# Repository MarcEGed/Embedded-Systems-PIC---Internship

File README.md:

Space invaders embedded systems project
Includes drivers, api, scheduler and main file

Written for PIC18F46K22

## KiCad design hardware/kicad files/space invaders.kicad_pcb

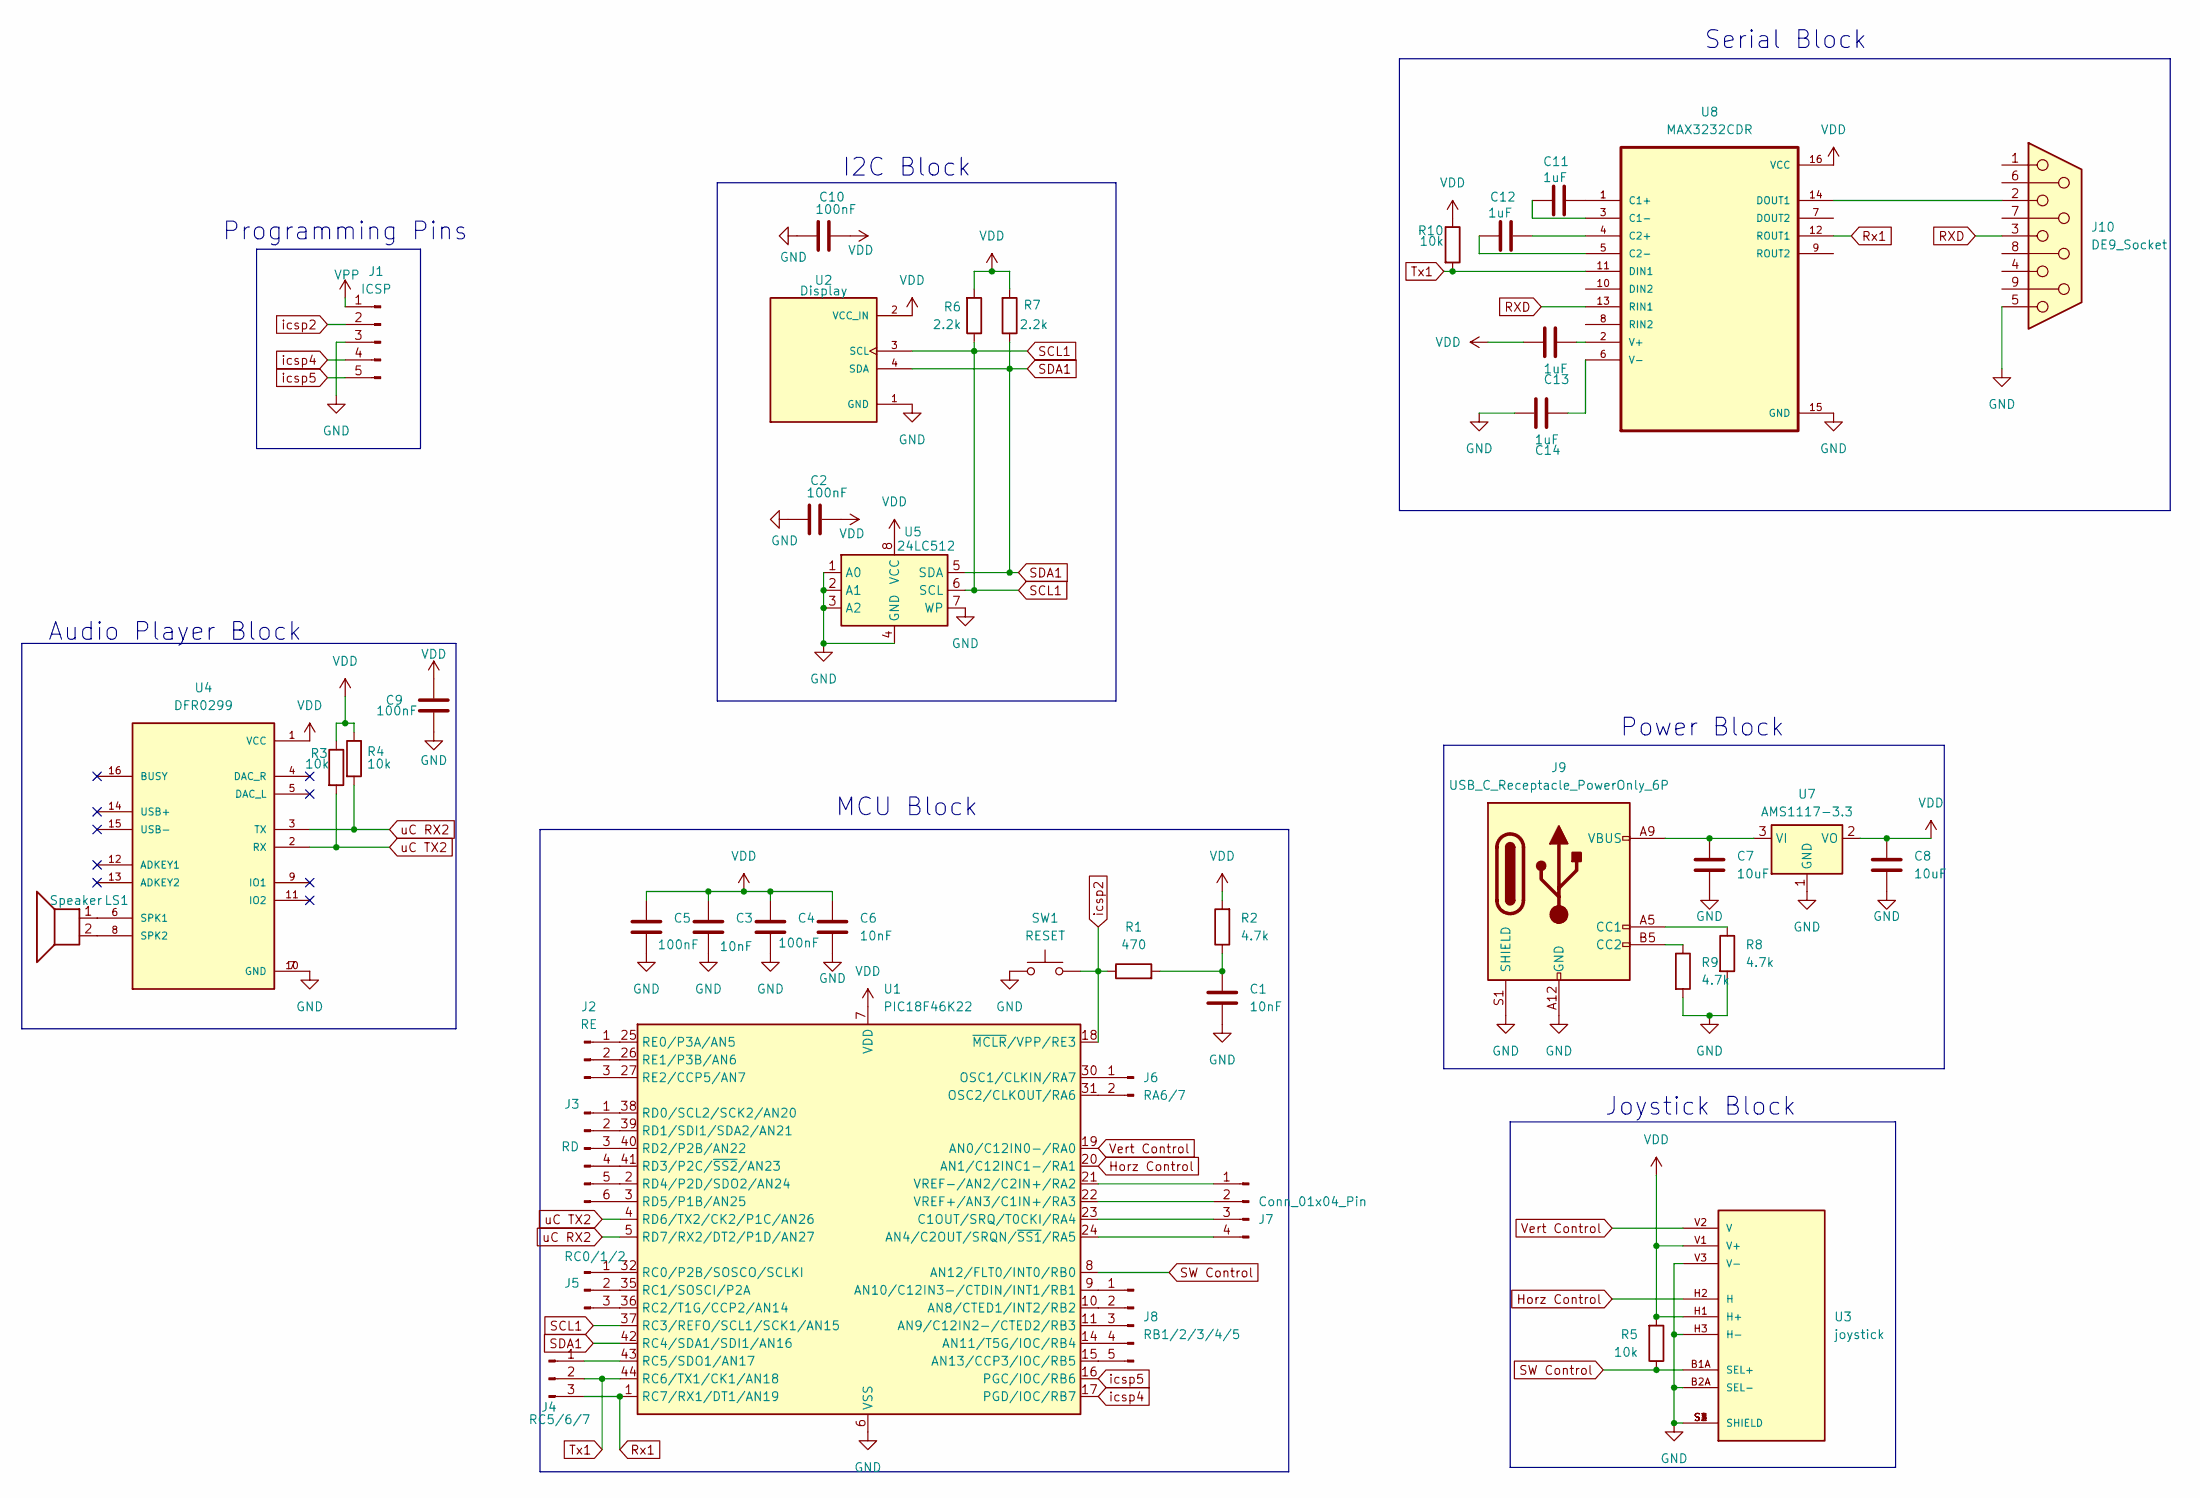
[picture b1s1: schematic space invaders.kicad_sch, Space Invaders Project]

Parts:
C1, C3, C6: 10nF; C_0603_1608Metric
C2, C4, C5, C9, C10: 100nF; C_0603_1608Metric
C7, C8: 10uF; C_0603_1608Metric
C11, C12, C13, C14: 1uF; C_0603_1608Metric
J1: ICSP; PinHeader_1x05_P2.54mm_Vertical
J2: RE; PinHeader_1x03_P2.54mm_Vertical
J3: RD; PinHeader_1x06_P2.54mm_Vertical
J4: RC5/6/7; PinHeader_1x03_P2.54mm_Vertical
J5: RC0/1/2; PinHeader_1x03_P2.54mm_Vertical
J6: RA6/7; PinHeader_1x02_P2.54mm_Vertical
J7: Conn_01x04_Pin; PinHeader_1x04_P2.54mm_Vertical
J8: RB1/2/3/4/5; PinHeader_1x05_P2.54mm_Vertical
J9: USB_C_Receptacle_PowerOnly_6P; USB_C_Receptacle_Amphenol_12401610E4-2A
J10: DE9_Socket; DSUB-9_Pins_Horizontal_P2.77x2.84mm_EdgePinOffset7.70mm_Hou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
LS1: Speaker; Speaker_CUI_CMR-1206S-67
R1: 470; R_0603_1608Metric
R2, R8, R9: 4.7k; R_0603_1608Metric
R3, R4, R5, R10: 10k; R_0603_1608Metric
R6, R7: 2.2k; R_0603_1608Metric
SW1: RESET; SW_PUSH_6mm_H4.3mm
U1: PIC18F46K22; TQFP-44_10x10mm_P0.8mm
U2: Display; MODULE_DM-OLED096-636; PARTREV 2018-09-10
U3: joystick; XDCR_COM-09032; PARTREV N/A
U4: DFR0299; MODULE_DFR0299
U5: 24LC512; SOIC-8-1EP_3.9x4.9mm_P1.27mm_EP2.41x3.3mm
U7: AMS1117-3.3; SOT-223-3_TabPin2
U8: MAX3232CDR; SOIC-16_3.9x9.9mm_P1.27mm

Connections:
GND: C1.2, C2.2, C3.2, C4.2, C5.2, C6.2, C7.1, C8.2, C9.2, C10.2, C14.1, J1.3, J9.A12 (GND), J9.B12 (GND), J9.S1 (SHIELD), J10.5, R8.2, R9.2, SW1.1, U1.6 (VSS), U1.29 (VSS), U2.1 (GND), U3.B2A (SEL-), U3.H3 (H-), U3.S1 (SHIELD), U3.S2 (SHIELD), U3.S3 (SHIELD), U3.S4 (SHIELD), U3.V3 (V-), U4.7 (GND), U4.10 (GND), U5.1 (A0), U5.2 (A1), U5.3 (A2), U5.4 (GND), U5.7 (WP), U7.1 (GND), U8.15 (GND)
Horz Control: U1.20 (AN1/C12INC1-/RA1), U3.H2 (H)
unnamed: C1.1, R1.2, R2.1
unnamed: J2.1, U1.25 (RE0/P3A/AN5)
unnamed: J2.2, U1.26 (RE1/P3B/AN6)
unnamed: J2.3, U1.27 (RE2/CCP5/AN7)
unnamed: J3.1, U1.38 (RD0/SCL2/SCK2/AN20)
unnamed: J3.2, U1.39 (RD1/SDI1/SDA2/AN21)
unnamed: J3.3, U1.40 (RD2/P2B/AN22)
unnamed: J3.4, U1.41 (RD3/P2C/~SS2/AN23)
unnamed: J3.5, U1.2 (RD4/P2D/SDO2/AN24)
unnamed: J3.6, U1.3 (RD5/P1B/AN25)
unnamed: J4.1, U1.43 (RC5/SDO1/AN17)
unnamed: J5.1, U1.32 (RC0/P2B/SOSCO/SCLKI)
unnamed: J5.2, U1.35 (RC1/SOSCI/P2A)
unnamed: J5.3, U1.36 (RC2/T1G/CCP2/AN14)
unnamed: J6.1, U1.30 (OSC1/CLKIN/RA7)
unnamed: J6.2, U1.31 (OSC2/CLKOUT/RA6)
unnamed: J7.1, U1.21 (VREF-/AN2/C2IN+/RA2)
unnamed: J7.2, U1.22 (VREF+/AN3/C1IN+/RA3)
unnamed: J7.3, U1.23 (C1OUT/SRQ/T0CKI/RA4)
unnamed: J7.4, U1.24 (AN4/C2OUT/SRQN/~SS1/RA5)
unnamed: J8.1, U1.9 (AN10/C12IN3-/CTDIN/INT1/RB1)
unnamed: J8.2, U1.10 (AN8/CTED1/INT2/RB2)
unnamed: J8.3, U1.11 (AN9/C12IN2-/CTED2/RB3)
unnamed: J8.4, U1.14 (AN11/T5G/IOC/RB4)
unnamed: J8.5, U1.15 (AN13/CCP3/IOC/RB5)
unnamed: J9.A5 (CC1), R8.1
unnamed: J9.B5 (CC2), R9.1
unnamed: LS1.1, U4.6 (SPK1)
unnamed: LS1.2, U4.8 (SPK2)
unnamed: C7.2, J9.A9 (VBUS), J9.B9 (VBUS), U7.3 (VI)
unnamed: C11.1, U8.1 (C1+)
unnamed: C11.2, U8.3 (C1-)
unnamed: C12.1, U8.4 (C2+)
unnamed: C12.2, U8.5 (C2-)
unnamed: J10.2, U8.14 (DOUT1)
unnamed: C13.2, U8.2 (V+)
unnamed: C14.2, U8.6 (V-)
RXD: J10.3, U8.13 (RIN1)
Rx1: J4.3, U1.1 (RC7/RX1/DT1/AN19), U8.12 (ROUT1)
SCL1: R6.1, U1.37 (RC3/REFO/SCL1/SCK1/AN15), U2.3 (SCL), U5.6 (SCL)
SDA1: R7.1, U1.42 (RC4/SDA1/SDI1/AN16), U2.4 (SDA), U5.5 (SDA)
SW Control: R5.1, U1.8 (AN12/FLT0/INT0/RB0), U3.B1A (SEL+)
Tx1: J4.2, R10.2, U1.44 (RC6/TX1/CK1/AN18), U8.11 (DIN1)
VDD: C2.1, C3.1, C4.1, C5.1, C6.1, C8.1, C9.1, C10.1, C13.1, R2.2, R3.1, R4.1, R5.2, R6.2, R7.2, R10.1, U1.7 (VDD), U1.28 (VDD), U2.2 (VCC_IN), U3.H1 (H+), U3.V1 (V+), U4.1 (VCC), U5.8 (VCC), U7.2 (VO), U8.16 (VCC)
VPP: J1.1
Vert Control: U1.19 (AN0/C12IN0-/RA0), U3.V2 (V)
icsp2: J1.2, R1.1, SW1.2, U1.18 (~MCLR/VPP/RE3)
icsp4: J1.4, U1.17 (PGD/IOC/RB7)
icsp5: J1.5, U1.16 (PGC/IOC/RB6)
uC RX2: R4.2, U1.5 (RD7/RX2/DT2/P1D/AN27), U4.3 (TX)
uC TX2: R3.2, U1.4 (RD6/TX2/CK2/P1C/AN26), U4.2 (RX)

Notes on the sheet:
Serial Block
Joystick Block
Audio Player Block
Programming Pins
Power Block
MCU Block
I2C Block

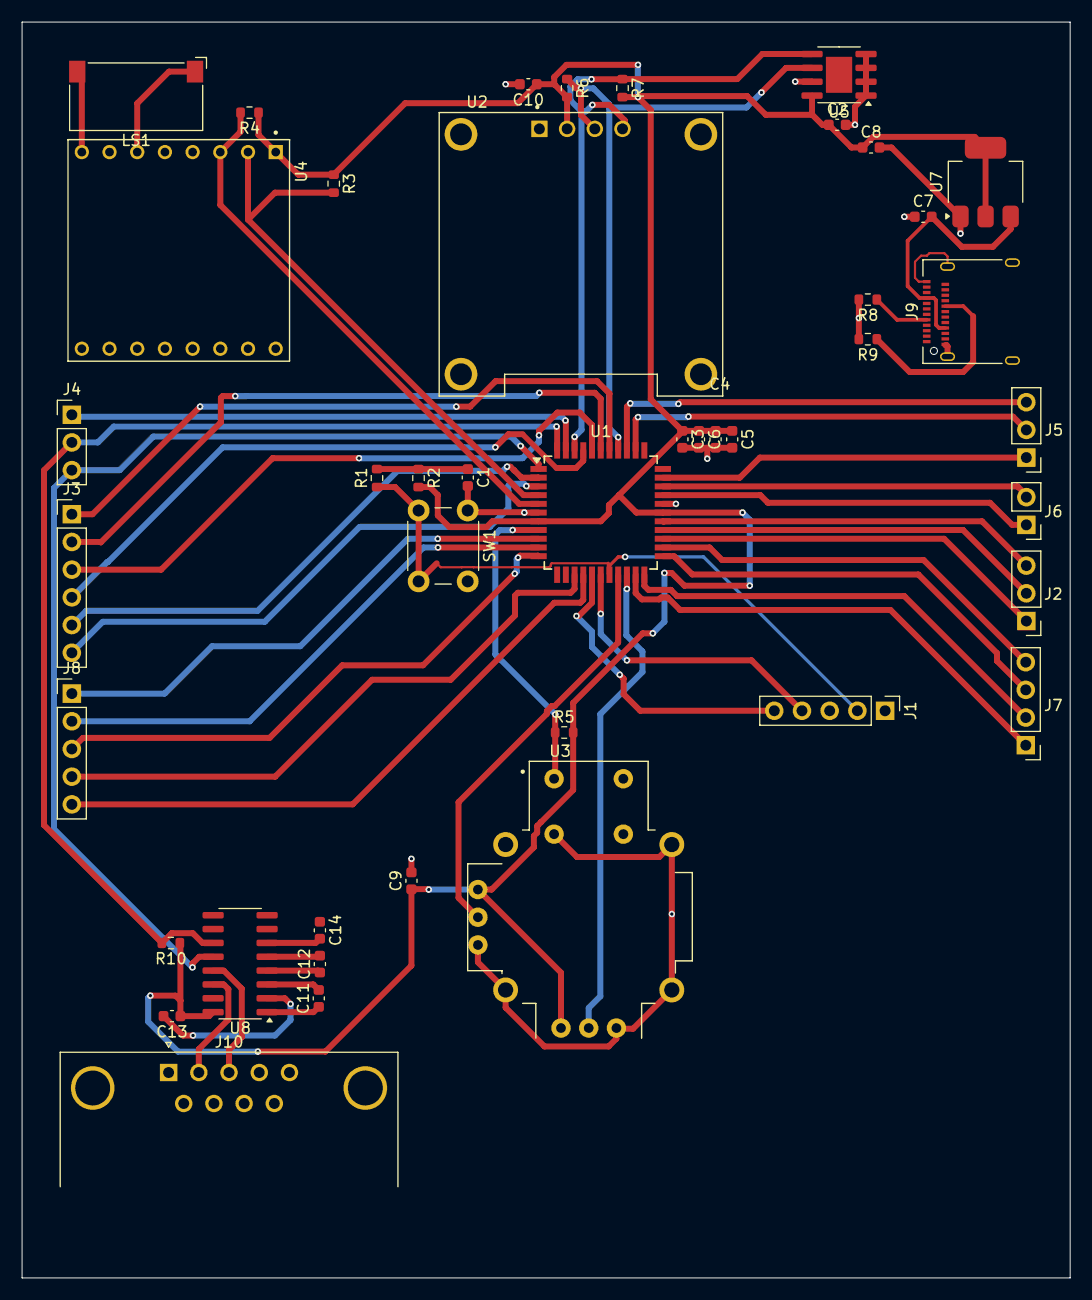
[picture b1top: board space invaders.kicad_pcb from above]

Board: 2 copper layers, 96.1 x 115.2 mm, 43 parts (0 on the bottom side), 52 nets.

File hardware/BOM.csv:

Reference,Qty,Value,DNP,Exclude from BOM,Exclude from Board,Footprint,Datasheet
"C1,C3,C6",3,10nF,,,,Capacitor_SMD:C_0603_1608Metric,~
"C2,C4,C5,C9,C10",5,100nF,,,,Capacitor_SMD:C_0603_1608Metric,~
"C7,C8",2,10uF,,,,Capacitor_SMD:C_0603_1608Metric,~
"C11,C12,C13,C14",4,1uF,,,,Capacitor_SMD:C_0603_1608Metric,~
J1,1,ICSP,,,,Connector_PinHeader_2.54mm:PinHeader_1x05_P2.54mm_Vertical,~
J2,1,RE,,,,Connector_PinHeader_2.54mm:PinHeader_1x03_P2.54mm_Vertical,~
J3,1,RD,,,,Connector_PinHeader_2.54mm:PinHeader_1x06_P2.54mm_Vertical,~
J4,1,RC5/6/7,,,,Connector_PinHeader_2.54mm:PinHeader_1x03_P2.54mm_Vertical,~
J5,1,RC0/1/2,,,,Connector_PinHeader_2.54mm:PinHeader_1x03_P2.54mm_Vertical,~
J6,1,RA6/7,,,,Connector_PinHeader_2.54mm:PinHeader_1x02_P2.54mm_Vertical,~
J7,1,Conn_01x04_Pin,,,,Connector_PinHeader_2.54mm:PinHeader_1x04_P2.54mm_Vertical,~
J8,1,RB1/2/3/4/5,,,,Connector_PinHeader_2.54mm:PinHeader_1x05_P2.54mm_Vertical,~
J10,1,DE9_Socket,,,,Connector_Dsub:DSUB-9_Pins_Horizontal_P2.77x2.84mm_EdgePinOffset7.70mm_Housed_MountingHolesOffset9.12mm,~
J11,1,speaker,,,,Connector_PinSocket_2.54mm:PinSocket_1x02_P2.54mm_Vertical,~
J12,1,Jack-DC,,,,Connector_BarrelJack:BarrelJack_Horizontal,~
R1,1,470,,,,Resistor_SMD:R_0603_1608Metric,~
R2,1,4.7k,,,,Resistor_SMD:R_0603_1608Metric,~
"R3,R4,R5,R10",4,10k,,,,Resistor_SMD:R_0603_1608Metric,~
"R6,R7",2,2.2k,,,,Resistor_SMD:R_0603_1608Metric,~
SW1,1,RESET,,,,Button_Switch_THT:SW_PUSH_6mm_H4.3mm,~
U1,1,PIC18F46K22,,,,Package_QFP:TQFP-44_10x10mm_P0.8mm,http://ww1.microchip.com/downloads/en/DeviceDoc/40001412G.pdf
U2,1,Display,,,,SH1106:MODULE_DM-OLED096-636,
U3,1,joystick,,,,COM_Joystick:XDCR_COM-09032,
U4,1,DFR0299,,,,MODULE_DFR0299:MODULE_DFR0299,
U5,1,24LC512,,,,Package_SO:SOIC-8-1EP_3.9x4.9mm_P1.27mm_EP2.41x3.3mm,http://ww1.microchip.com/downloads/en/DeviceDoc/21754M.pdf
U7,1,AMS1117-3.3,,,,Package_TO_SOT_SMD:SOT-223-3_TabPin2,http://www.advanced-monolithic.com/pdf/ds1117.pdf
U8,1,MAX3232CDR,,,,Package_SO:SOIC-16_3.9x9.9mm_P1.27mm,

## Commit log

2025-08-12 Initial full reupload
2025-08-12 moved output folder
2025-08-12 ignored all _history folders
2025-08-12 removed all _history folders
2025-08-12 Removed __history folders
2025-08-12 Clean-up
2025-08-16 Main now only initializes and runs scheduler
2025-08-19 Cleaned up main
2025-08-21 Added an empty project as a starting point (+scheduler +i2c +adc)
2025-08-22 Added PoC simulation
2025-08-22 Fixed few types
2025-08-22 Fixed few typos
2025-08-25 Added remaining c files
2025-08-26 Added i2c PoC
2025-08-26 intermediate commit
2025-08-26 EEPROM i2c testing
2025-08-26 working eeprom and joystick
2025-08-26 Fixed Joystick issue
2025-08-26 Screen issue solved (thank you Majdi)
2025-08-27 Cleaned up files
2025-08-27 Added tasks
2025-08-27 Added POC for adc for debug
2025-08-27 Minor bug fixes
2025-08-27 Task creation is no longer in main
2025-08-27 Fixed ADC issue
2025-08-28 added mp3 driver and audio api to project folder
2025-08-28 Inverted Y player control for convenience
2025-08-29 Fixed inverted Y bug
2025-08-29 Fixed joystick driver to use live adc and not average
2025-08-29 Fixed game loop rendering quickly before start screen
2025-09-09 added dfplayer driver
2025-09-17 Fixed the DFPlayer problem
2025-09-17 Added audio api and finalized tasks
2025-09-17 Cleaned up and added comments
2025-12-10 added hardware
2026-02-06 added serial, need to fix pcb
2026-02-06 Added Serial to PCB
2026-02-12 Exported all newest versions
2026-02-16 Replaced speaker
2026-02-17 reexported with minor fixes
2026-02-17 cleaner export gerb
2026-02-17 even more cleaning
2026-02-17 final fixes(?)
